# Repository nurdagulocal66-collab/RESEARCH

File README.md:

# RESEARCH
Bu proje, çok kademeli güç yönetimi ve regülasyon işlemlerini tek bir kart üzerinde toplamak amacıyla geliştirilmiş kapsamlı bir donanım tasarımının şematik altyapısını oluşturmaktadır. Çalışma prensibi olarak sistem, ana giriş gerilimini LM5576 tabanlı anahtarlamalı regülatör (buck converter) yapısı kullanarak verimli bir şekilde düşürmekte ve 500 kHz anahtarlama frekansı hedefiyle güç ağını beslemektedir. Elde edilen bu ara gerilim seviyelerinin ardından, kart üzerinde konumlandırılan LM1117-5.0 ve LT1117-3.3 lineer regülatörler (LDO) aracılığıyla hassas devreler ve mikrodenetleyici birimleri için kararlı 5V ve 3.3V DC besleme rayları türetilmektedir. Tasarımda yer alan IR2101 gate sürücü ve STP75NF75 güç MOSFET yapıları ile M7-HT diyotlar gibi çevre elemanlar ise doğrudan regülasyon döngüsünü destekleyen anahtarlama ve kontrol kademelerini oluşturmakta, ayrıca devredeki TestPoint noktaları ve montaj padleri sistemin test edilebilirliğini ve fiziksel kararlılığını güvence altına almaktadır.

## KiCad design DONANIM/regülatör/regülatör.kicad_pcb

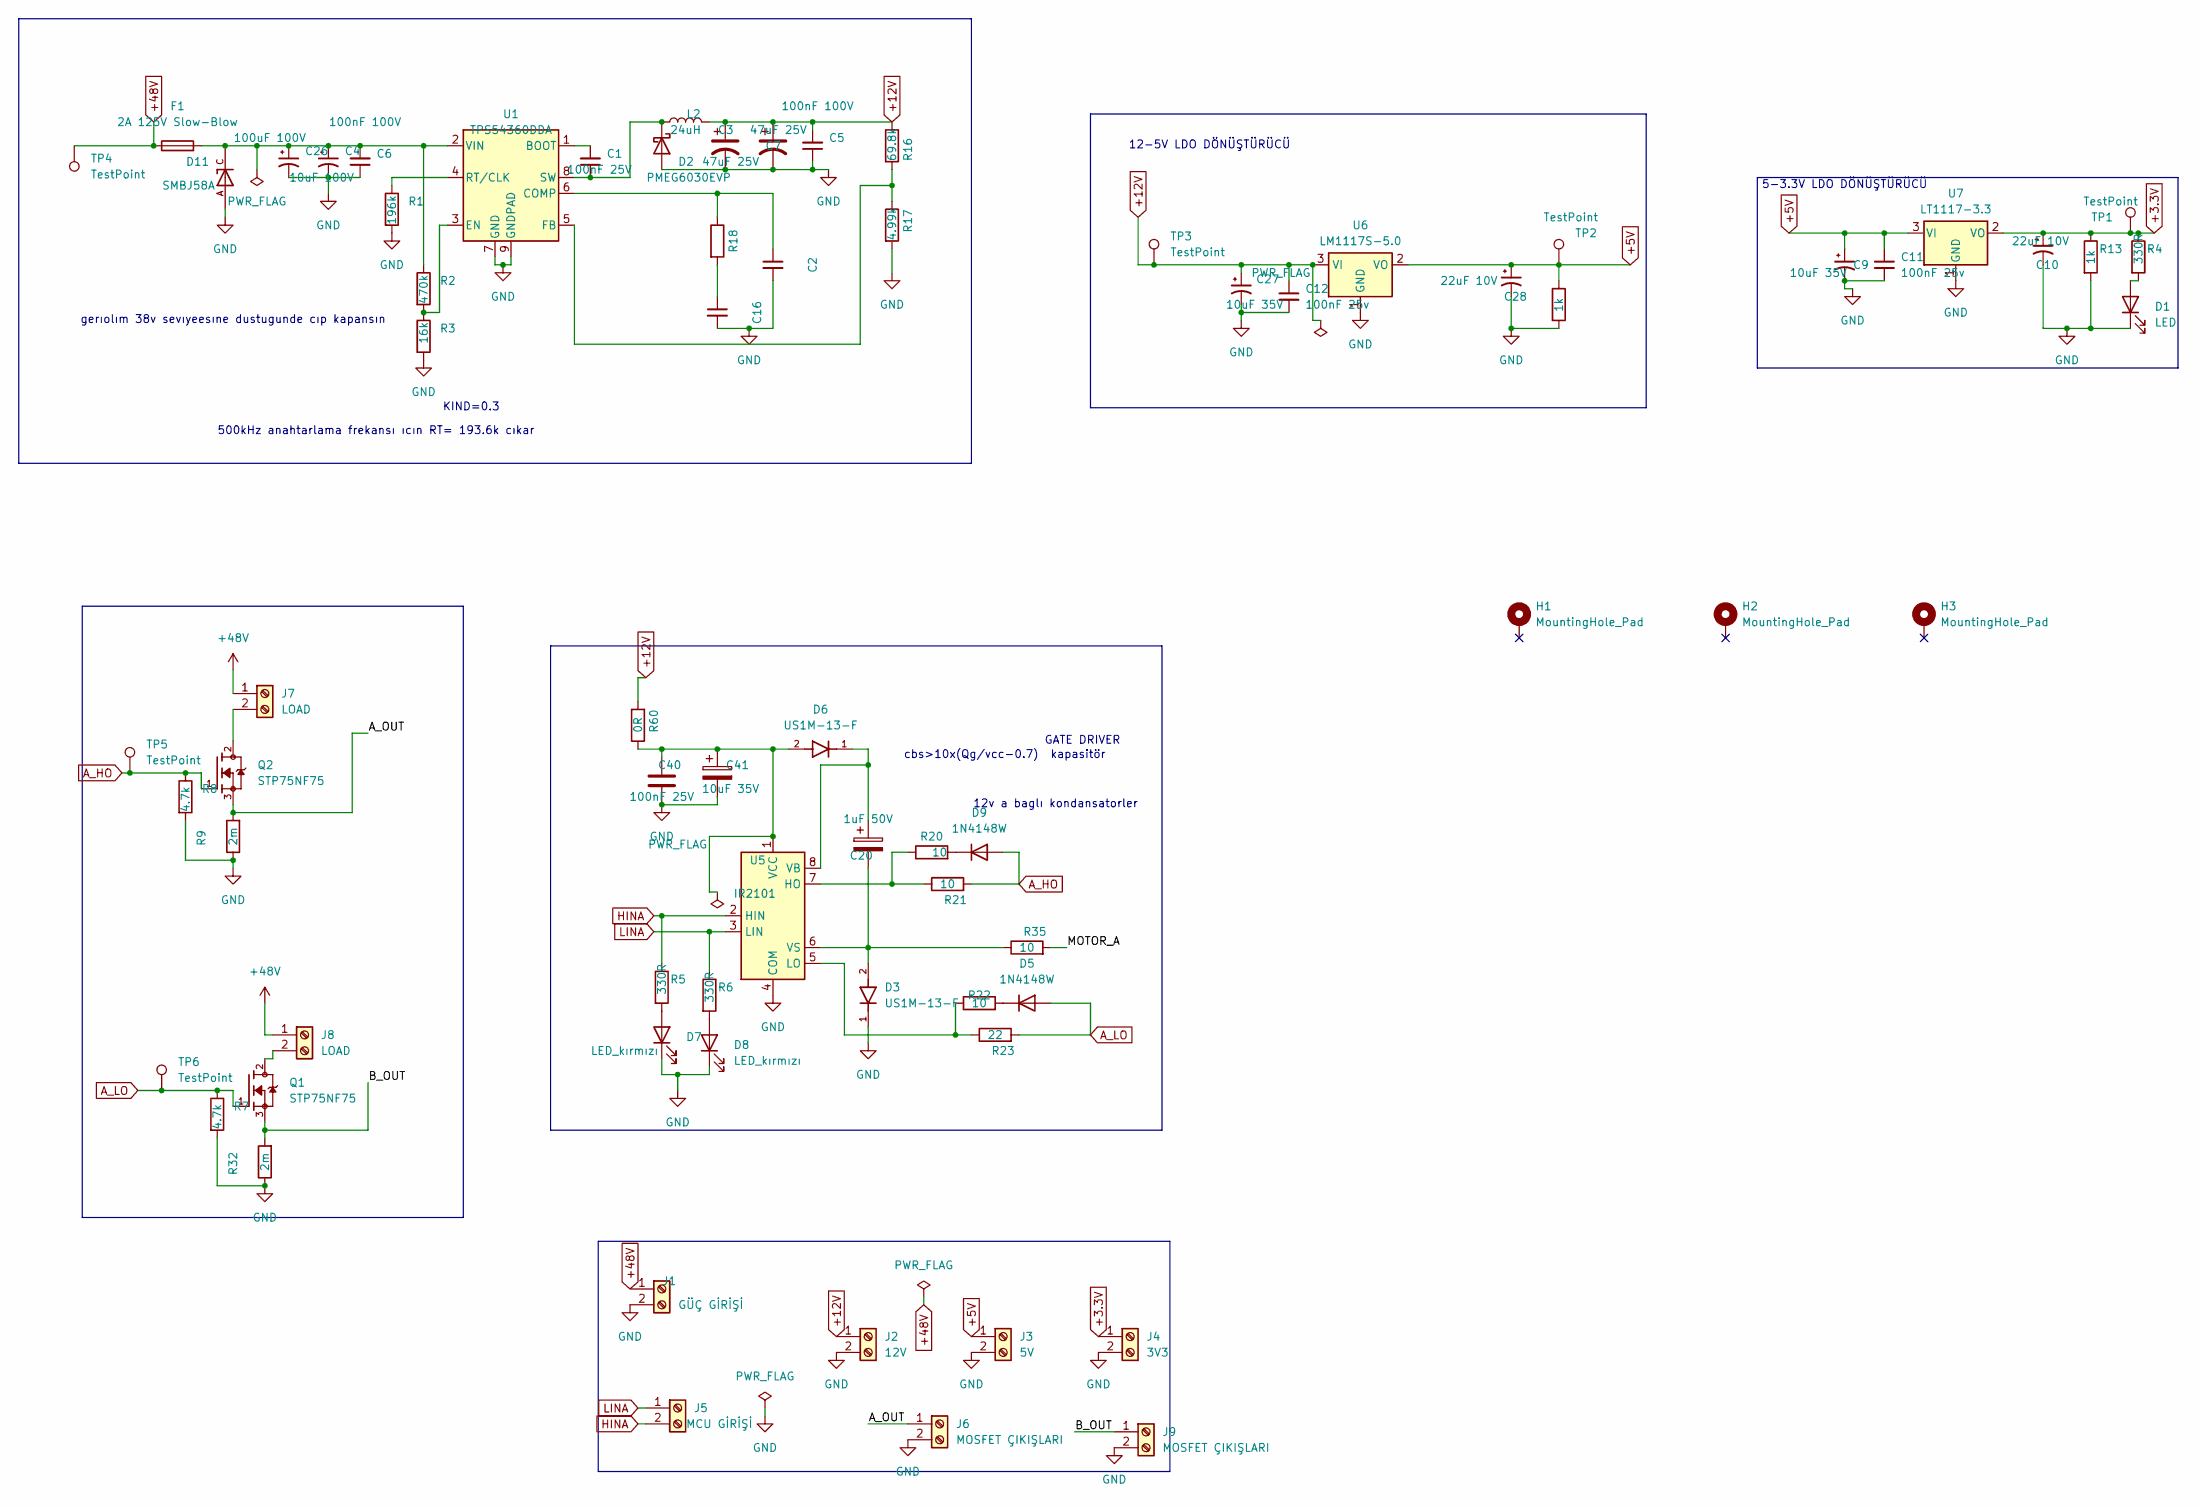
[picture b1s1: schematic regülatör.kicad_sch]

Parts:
C1, C40: 100nF 25V; C_0805_2012Metric
C2: 22pF 25V; C_0402_1005Metric
C3, C7: 47uF 25V; CP_Radial_D8.0mm_P5.00mm
C4: 10uF 100V; CP_Radial_D10.0mm_P5.00mm
C5: 100nF 100V; C_0805_2012Metric
C6: 100nF 100V; C_1206_3216Metric
C9, C27, C41: 10uF 35V; CP_Elec_5x5.3
C10, C28: 22uF 10V; CP_Elec_4x5.3
C11, C12: 100nF 25v; C_0805_2012Metric
C16: 4.7nF 25V; C_0805_2012Metric
C20: 1uF 50V; CP_Elec_4x5.3
C26: 100uF 100V; CP_Radial_D10.0mm_P5.00mm
D1: LED; LED_0805_2012Metric
D2: PMEG6030EVP; D_SOD-128
D3, D6: US1M-13-F; D_SMA; PARTREV 11-2
D5, D9: 1N4148W; D_SOD-123
D7, D8: LED_kırmızı; LED_0805_2012Metric
D11: SMBJ58A; D_SMB; PARTREV F2102
F1: 2A 125V Slow-Blow; Fuse_Littelfuse_395Series
H1, H2, H3: MountingHole_Pad; MountingHole_3.2mm_M3_DIN965_Pad
J1: GÜÇ GİRİŞİ; TerminalBlock_Phoenix_MKDS-1,5-2_1x02_P5.00mm_Horizontal
J2: 12V; TerminalBlock_Phoenix_MKDS-1,5-2_1x02_P5.00mm_Horizontal
J3: 5V; TerminalBlock_Phoenix_MKDS-1,5-2_1x02_P5.00mm_Horizontal
J4: 3V3; TerminalBlock_Phoenix_MKDS-1,5-2_1x02_P5.00mm_Horizontal
J5: MCU GİRİŞİ; TerminalBlock_Phoenix_MKDS-1,5-2_1x02_P5.00mm_Horizontal
J6, J9: MOSFET ÇIKIŞLARI; TerminalBlock_Phoenix_MKDS-1,5-2_1x02_P5.00mm_Horizontal
J7, J8: LOAD; TerminalBlock_Phoenix_MKDS-1,5-2_1x02_P5.00mm_Horizontal
L2: 24uH; L_12x12mm_H8mm
Q1, Q2: STP75NF75; PinSocket_1x03_P2.54mm_Vertical
R1: 196k; R_0603_1608Metric
R2: 470k; R_0805_2012Metric
R3: 16k; R_0805_2012Metric
R4, R5, R6: 330R; R_0603_1608Metric
R7, R8: 4.7k; R_0805_2012Metric
R9, R32: 2m; R_4020_10251Metric
R13: 1k; C_0402_1005Metric
R16: 69.8k; R_0805_2012Metric
R17: 4.99k; R_0805_2012Metric
R18: 47k; R_0805_2012Metric
R20, R21, R22, R35: 10; R_0805_2012Metric
R23: 22; R_0805_2012Metric
R47: 1k; R_0805_2012Metric
R60: 0R; R_0805_2012Metric
TP1, TP2, TP3, TP4, TP5, TP6: TestPoint; TestPoint_Pad_D2.0mm
U1: TPS54360DDA; TI_SO-PowerPAD-8_ThermalVias
U5: IR2101; SOIC-8_3.9x4.9mm_P1.27mm
U6: LM1117S-5.0; SOT-223-3_TabPin2
U7: LT1117-3.3; SOT-223-3_TabPin2

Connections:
+3.3V: C10.1, J4.1, R4.1, R13.1, TP1.1, U7.2 (VO)
+5V: C9.1, C11.1, C28.1, J3.1, R47.1, TP2.1, U6.2 (VO), U7.3 (VI)
+12V: C3.1, C5.2, C7.1, C12.1, C27.1, J2.1, L2.2, R16.1, R60.2, TP3.1, U6.3 (VI)
+48V: F1.1, J1.1, J7.1, J8.1, TP4.1
/A_OUT: J6.1, Q2.3, R9.2
/B_OUT: J9.1, Q1.3, R32.2
/MOTOR_A: R35.2
A_HO: D9.2 (A), Q2.1, R8.1, R21.2, TP5.1
A_LO: D5.2 (A), Q1.1, R7.1, R23.2, TP6.1
GND: C2.2, C3.2, C4.2, C5.1, C6.1, C7.2, C9.2, C10.2, C11.2, C12.2, C16.2, C26.2, C27.2, C28.2, C40.1, C41.2, D1.1 (K), D2.2 (A), D3.1, D7.1 (K), D8.1 (K), D11.A, J1.2, J2.2, J3.2, J4.2, J6.2, J9.2, R1.2, R3.2, R7.2, R8.2, R9.1, R13.2, R17.2, R32.1, R47.2, U1.7 (GND), U1.9 (GNDPAD), U5.4 (COM), U6.1 (GND), U7.1 (GND)
HINA: J5.2, R5.1, U5.2 (HIN)
LINA: J5.1, R6.1, U5.3 (LIN)
unnamed: C16.1, R18.2
unnamed: D1.2 (A), R4.2
unnamed: C1.1, D2.1 (K), L2.1, U1.8 (SW)
unnamed: D5.1 (K), R22.2
unnamed: D7.2 (A), R5.2
unnamed: D8.2 (A), R6.2
unnamed: D9.1 (K), R20.2
unnamed: J7.2, Q2.2
unnamed: J8.2, Q1.2
unnamed: C1.2, U1.1 (BOOT)
unnamed: C2.1, R18.1, U1.6 (COMP)
unnamed: R2.2, R3.1, U1.3 (EN)
unnamed: R16.2, R17.1, U1.5 (FB)
unnamed: R1.1, U1.4 (RT/CLK)
unnamed: C4.1, C6.2, C26.1, D11.C, F1.2, R2.1, U1.2 (VIN)
unnamed: R20.1, R21.1, U5.7 (HO)
unnamed: R22.1, R23.1, U5.5 (LO)
unnamed: C20.1, D6.1, U5.8 (VB)
unnamed: C40.2, C41.1, D6.2, R60.1, U5.1 (VCC)
unnamed: C20.2, D3.2, R35.1, U5.6 (VS)

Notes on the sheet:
cbs>10x(Qg/vcc-0.7) kapasitör
GATE DRIVER
gerıolım 38v sevıyeesıne dustugunde cıp kapansın
5-3.3V LDO DÖNÜŞTÜRÜCÜ
KIND=0.3
12-5V LDO DÖNÜŞTÜRÜCÜ
12v a baglı kondansatorler
500kHz anahtarlama frekansı ıcın RT= 193.6k cıkar

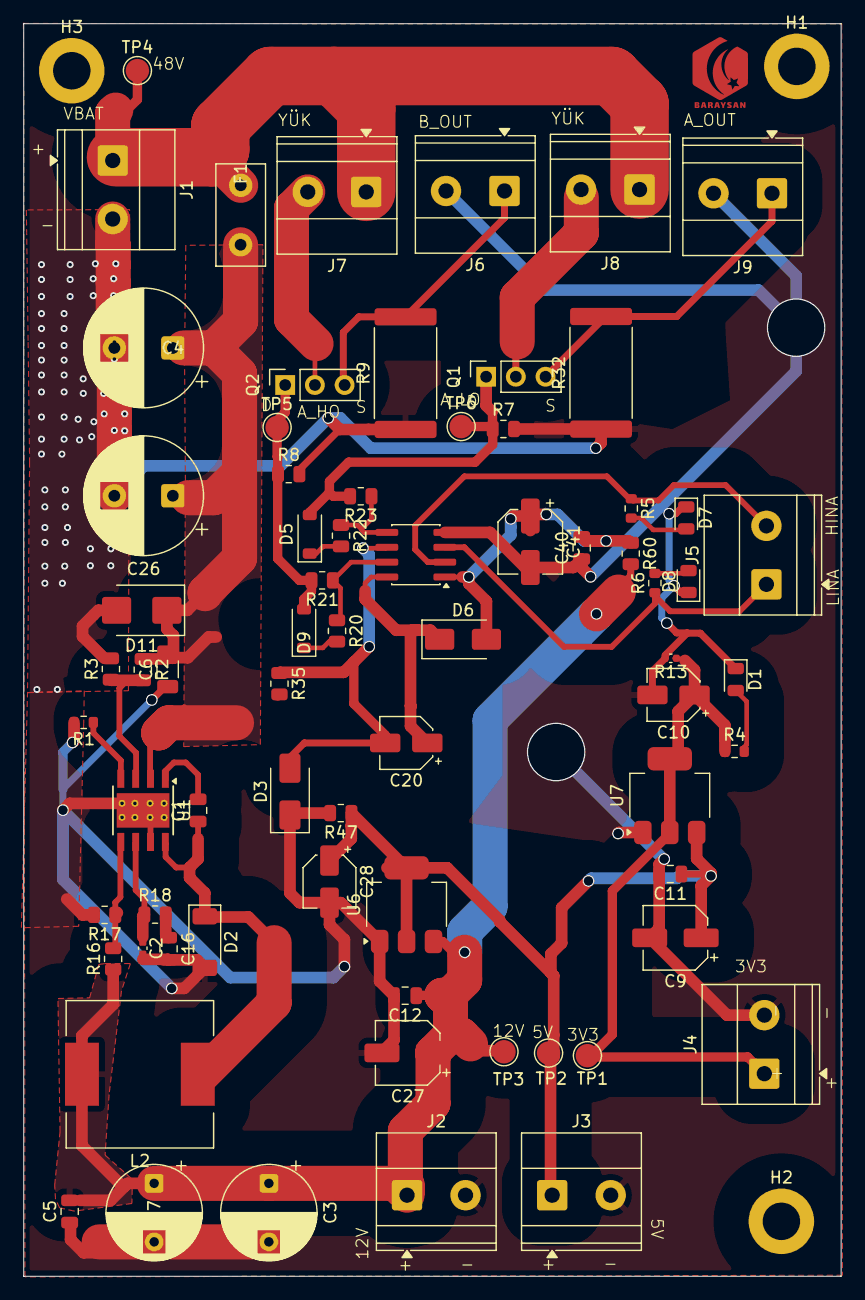
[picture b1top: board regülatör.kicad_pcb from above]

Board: 2 copper layers, 69.9 x 107.1 mm, 74 parts (0 on the bottom side), 31 nets.
